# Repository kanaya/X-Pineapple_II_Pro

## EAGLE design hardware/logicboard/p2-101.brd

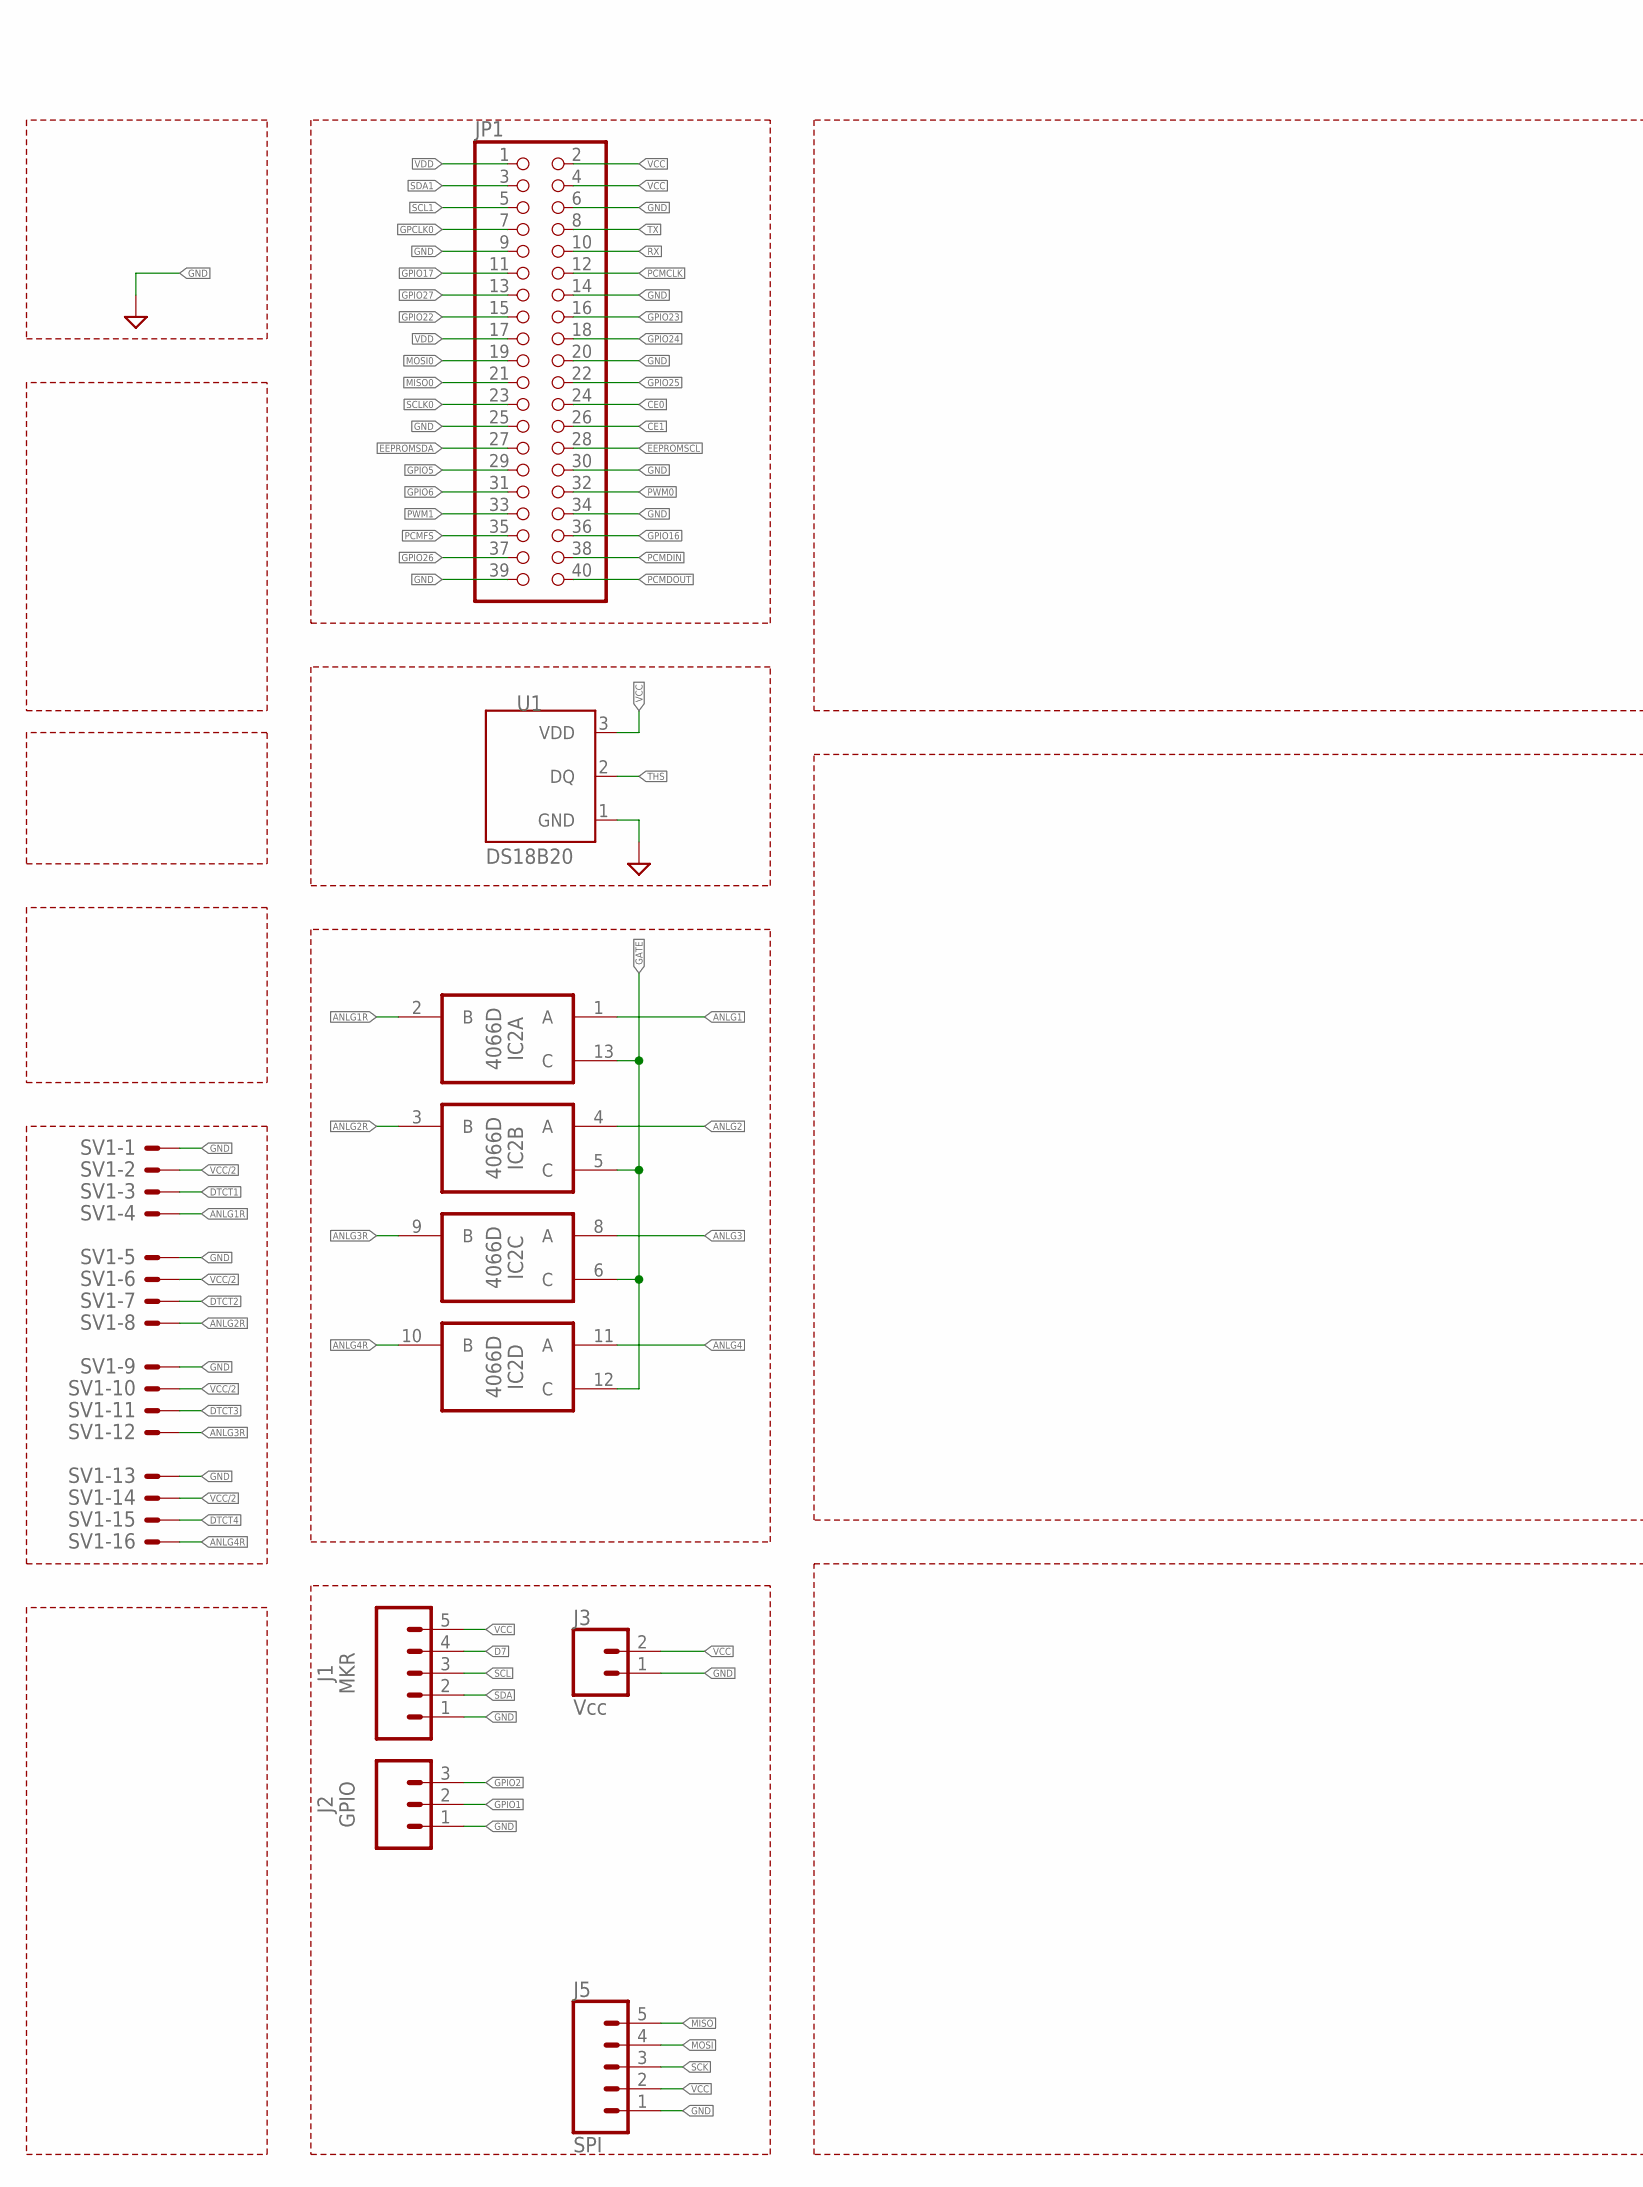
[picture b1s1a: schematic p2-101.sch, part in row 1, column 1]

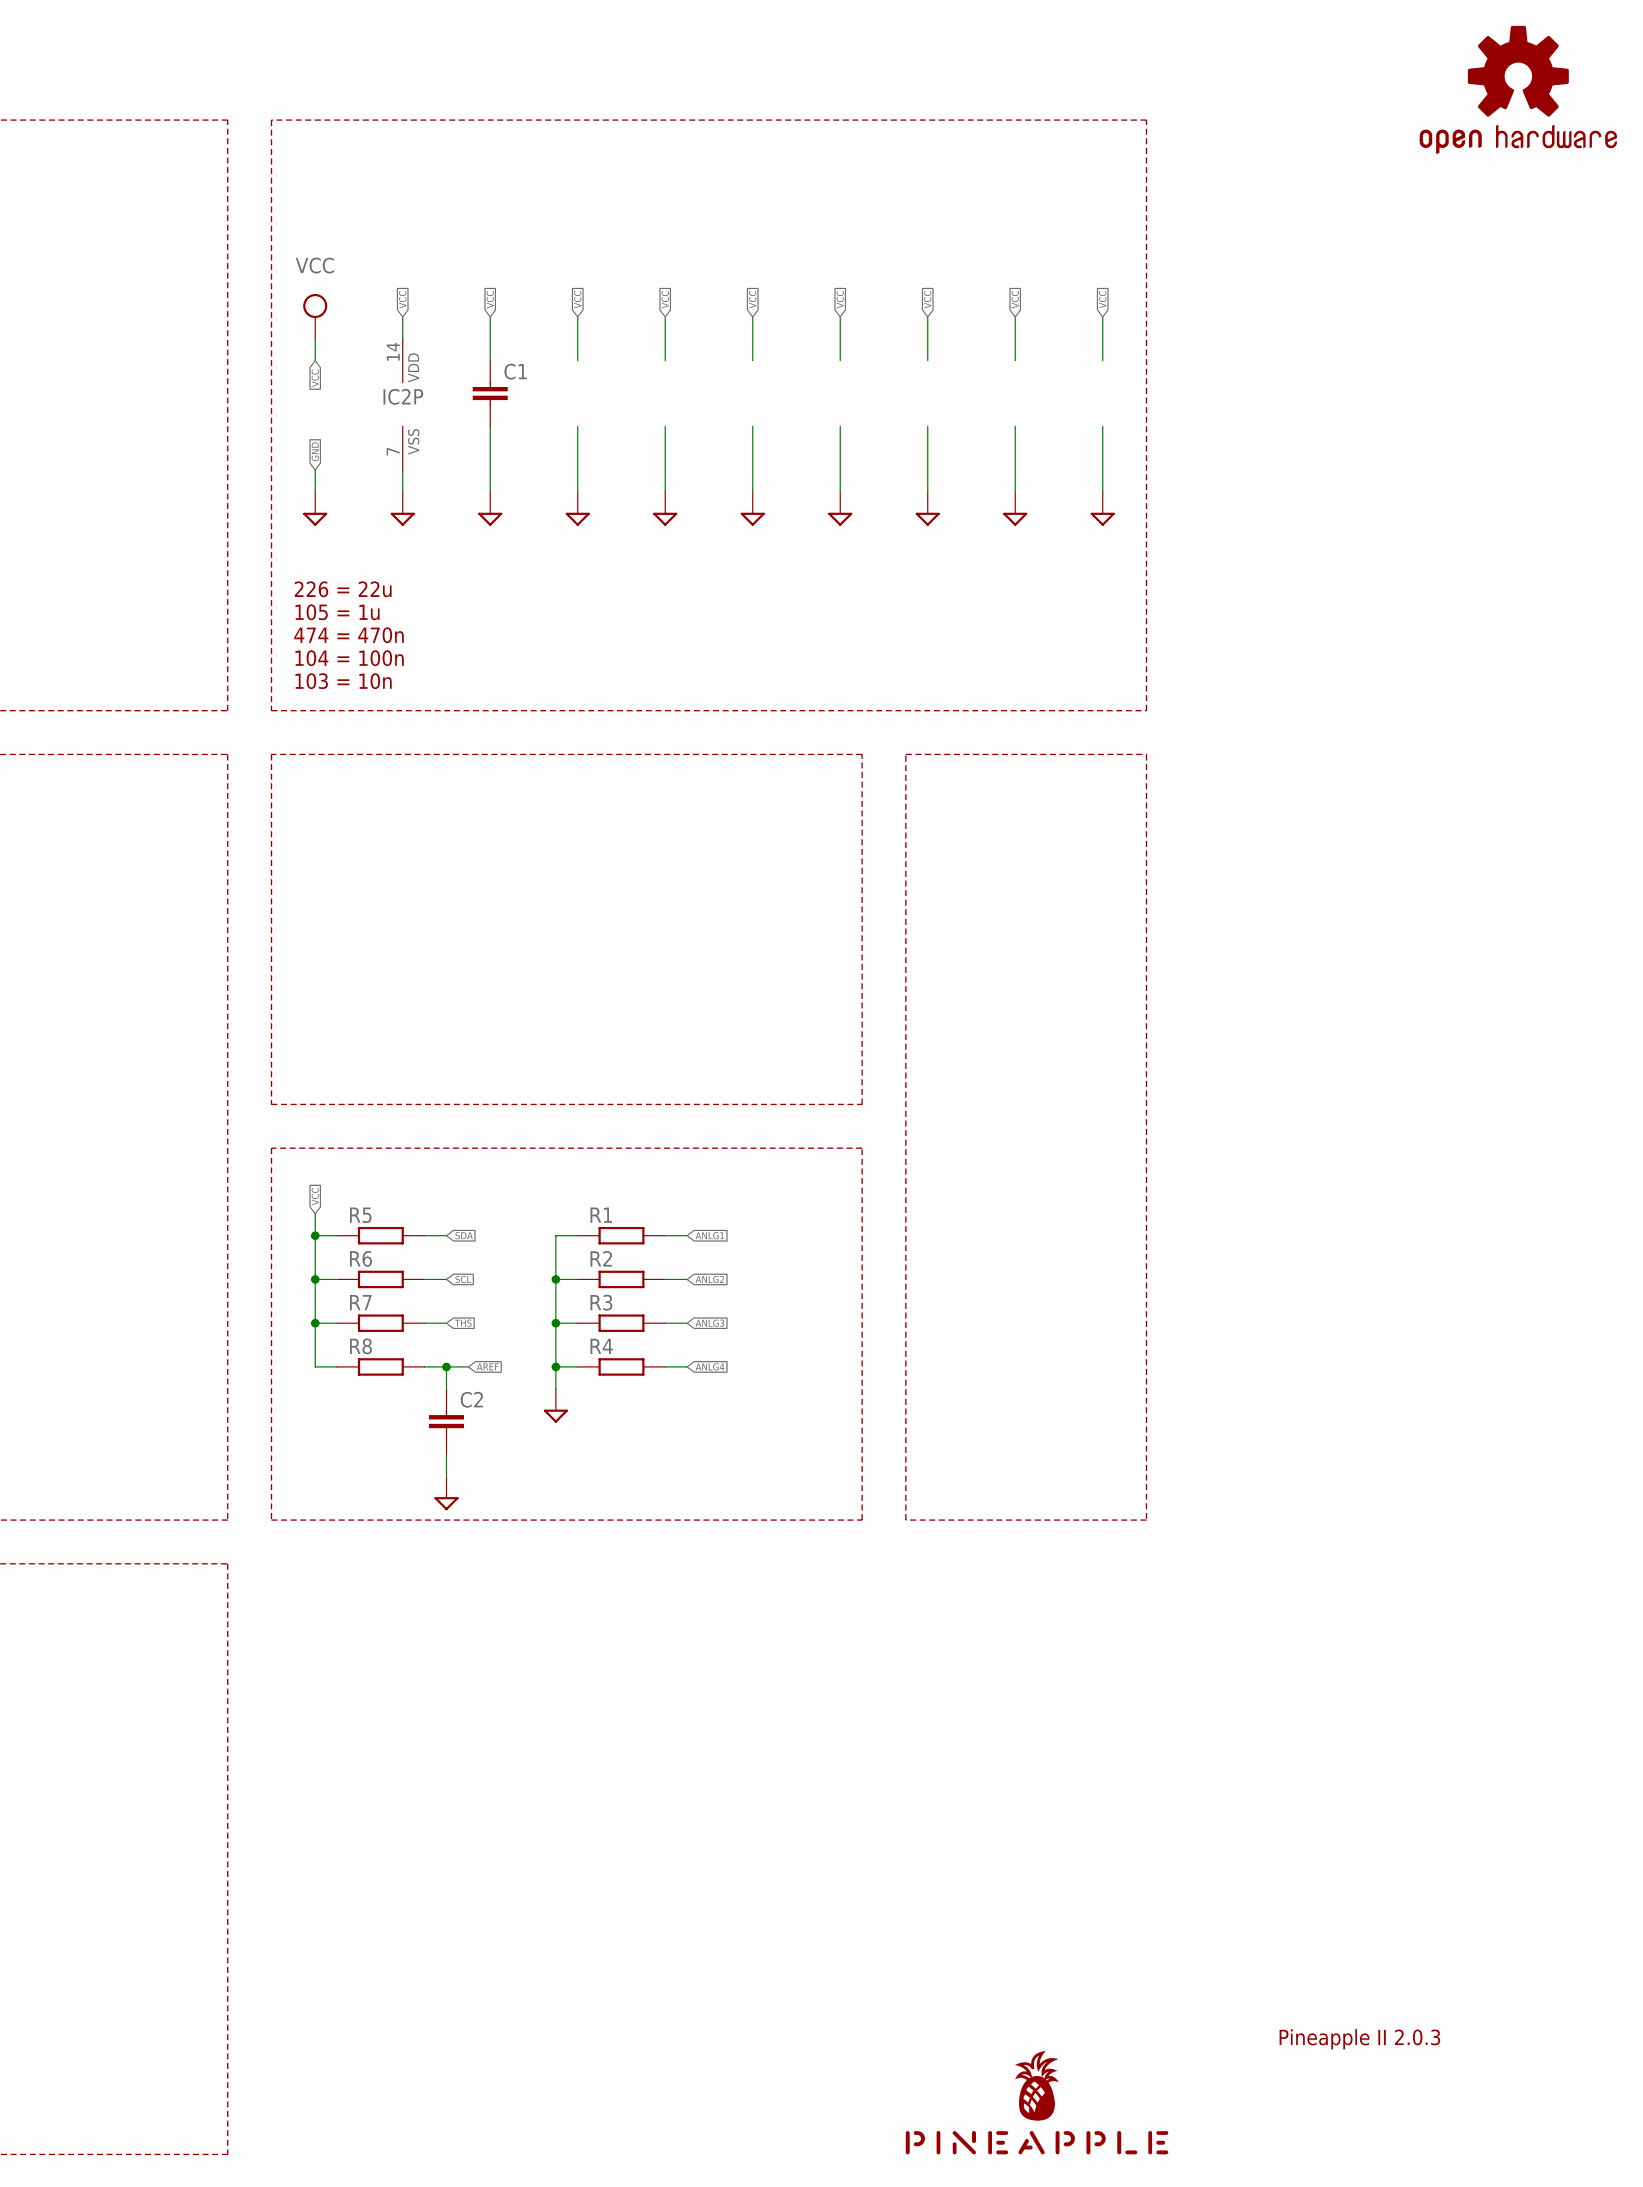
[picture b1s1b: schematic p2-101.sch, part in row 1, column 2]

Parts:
C1, C2: C-EUC2012; C2012
IC2: 4066D; SO14
J1: MKR; JST-5-PTH
J2: GPIO; JST-3-PTH
J3: Vcc; JST-2-PTH
J5: SPI; JST-5-PTH-VERT
JP1: PINHD-2X20; 2X20
LOGO1: OSHW-LOGOS-COPPER; OSHW-LOGO-S_COPPER
R1, R2, R3, R4, R5, R6, R7, R8: R-EU_M2012; M2012
SV1: ML16LE; ML16L
U1: DS18B20; TO-92-AMMO
U$1: PINEAPPLE450_SILK

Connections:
ANLG1: IC2.1 (A), R1.2
ANLG1R: IC2.2 (B), SV1.4
ANLG2: IC2.4 (A), R2.2
ANLG2R: IC2.3 (B), SV1.8
ANLG3: IC2.8 (A), R3.2
ANLG3R: IC2.9 (B), SV1.12
ANLG4: IC2.11 (A), R4.2
ANLG4R: IC2.10 (B), SV1.16
AREF: C2.1, R8.2
CE0: JP1.24
CE1: JP1.26
D7: J1.4
DTCT1: SV1.3
DTCT2: SV1.7
DTCT3: SV1.11
DTCT4: SV1.15
EEPROMSCL: JP1.28
EEPROMSDA: JP1.27
GATE: IC2.5 (C), IC2.6 (C), IC2.12 (C), IC2.13 (C)
GND: C1.2, C2.2, IC2.7 (VSS), J1.1, J2.1, J3.1, J5.1, JP1.6, JP1.9, JP1.14, JP1.20, JP1.25, JP1.30, JP1.34, JP1.39, R1.1, R2.1, R3.1, R4.1, SV1.1, SV1.5, SV1.9, SV1.13, U1.1 (GND)
GPCLK0: JP1.7
GPIO1: J2.2
GPIO2: J2.3
GPIO5: JP1.29
GPIO6: JP1.31
GPIO16: JP1.36
GPIO17: JP1.11
GPIO22: JP1.15
GPIO23: JP1.16
GPIO24: JP1.18
GPIO25: JP1.22
GPIO26: JP1.37
GPIO27: JP1.13
MISO: J5.5
MISO0: JP1.21
MOSI: J5.4
MOSI0: JP1.19
PCMCLK: JP1.12
PCMDIN: JP1.38
PCMDOUT: JP1.40
PCMFS: JP1.35
PWM0: JP1.32
PWM1: JP1.33
RX: JP1.10
SCK: J5.3
SCL: J1.3, R6.2
SCL1: JP1.5
SCLK0: JP1.23
SDA: J1.2, R5.2
SDA1: JP1.3
THS: R7.2, U1.2 (DQ)
TX: JP1.8
VCC: C1.1, IC2.14 (VDD), J1.5, J3.2, J5.2, JP1.2, JP1.4, R5.1, R6.1, R7.1, R8.1, U1.3 (VDD)
VCC/2: SV1.2, SV1.6, SV1.10, SV1.14
VDD: JP1.1, JP1.17

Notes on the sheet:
Pineapple II 2.0.3
226 = 22u 105 = 1u 474 = 470n 104 = 100n 103 = 10n

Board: 2 copper layers, 20 parts (0 on the bottom side), 17 nets, no tracks yet.

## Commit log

2021-03-22 Imported from Pineapple II 2.2.0-RC.
2021-03-22 Removed Arduino.
2022-08-29 Unknown...

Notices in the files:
parts and their libraries:
SparkFun-Aesthetics: Licensing: Creative Commons ShareAlike 4.0 International - https://creativecommons.org/licenses/by-sa/4.0
